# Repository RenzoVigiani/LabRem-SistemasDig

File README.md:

# Laboratorios de Sistemas digitales
En este readme se detallan las partes mas importantes del proyecto de remotización del laboratorio de **Sistemas digitales**, haciendo énfacis en el hardware.

## Protocolo para los laboratorios de "Sistemas Digitales"
Para poder establecer una comunicación entre al api web, generada por el equipo de software del proyecto, y los dispositivos en el laboratorio establecemos un protocolo en común. 

El procedimiento de comunicación es el siguiente.
Cada vez que se quiere modificar algun dato en el laboratorio. El Servidor debe enviar un...

```Ruby 
POST /HTTP/1.1 + <JSON a enviar>
```

##### Json a enviar (ejemplo)

```Ruby
{"Estado": [ 0, 1, 0],"velocidad": 9600, "Pulsadores": [0,1,1,0], "Serial": "Mensaje serial"}
```

Y para obtener avances de los datos o reporte de los datos debe enviar un:

```Ruby
GET /HTTP/1.1
```

De esta forma el Arduino responde ante una petición.

##### Json a recibir (ejemplo)

```Ruby
{"Estado": [ 0, true, false], "Velocidad":9600,"Indicadores": [false,false,false,false], "Serial": "Mensaje serial","Error":0}
```

## Sintaxis

**Estado**
Es un array conformado por 3 elementos en el siguiente orden: [Laboratorio, SubLab, Inicio del experimento]

|Laboratorio  | Sub Laboratorio  | Inicio del experimento | Laboratorio Seleccionado | Estado del experimento|
|-|-----|-----|------------------|--------|
|0|true |true |Comunicación UART |Inicia  |
|0|true |false|Comunicación UART |Finaliza|
|0|false|true |Comunicación I2C  |Inicia  |
|0|false|false|Comunicación I2C  |Finaliza|

>**Nota:** Los valores booleanos se los puede recibir en cualquier forma, es decir, <span style="color: green">_true=1=HIGH_ </span> y <span style="color: red">_false=0=LOW_</span>

**Velocidad**
Es un dato tipo entero que indica la velocidad de comunicación deseada.
*_ej: 9600, 115200, etc._

**Elementos por Laboratorio**
Laboratorio de UART

  - Utiliza **FPGA Cyclone II**    
    Nombre: Altera_FPGA_Board_EP2C8Q208C8 Cyclone II
    
  - Pulsadores: [Pulsador1, Pulsador2, Pulsador3, Pulsador4]
  - Indicadores: [indicador1, indicador2, indicador3, indicador4]

Laboratorio de I2C

  - Utiliza **FPGA Cyclone IV**
    Nombre: Altera_FPGA_Board_EP4CE6E22C8 Cyclone IV

  - Pulsadores: [Pulsador1, Pulsador2,Pulsador3,Pulsador4 ]
  - Indicadores:  [indicador1, indicador2, indicador3, indicador4]

>Los mismos son utilizados para representar en la API lo que se ve por la WebCam.

**Serial:** Es un dato del tipo "string" con un tamaño maximo de 100 caracteres.

**Error:** Es una variable numerica que representa un mensaje de error.

| Tipo de error                         |  Valor  |
| ----------------------------------    |---------|
| Sin errores                           |    0    |
| Error limites de angulo de azimut.    |    1    |
| Error limites de angulo de elevación  |    2    |
| Error de laboratorio incorrecto       |    3    |

## Diagramas

**Esquematico general**

**Esquematico**

**Arduino Mega 2560: Pin Out**

 **Adaptadores de nivel**

## *Diseños 3D*
Para cada una de las placas se realizaron bases y soportes para las placas para poder identificar a cada una y que se pueda diferencias con facilidad desde el usuario.

||||
|-|-|-|
||||
||||
||||
||||

**Datasheets**
- [Recopilación de Datasheets](https://renzovigiani.notion.site/adea4f735c994faaa2f919a7e5105e9d?v=83070c8c05d34c02905fc370e37b802a)
- [Altera Cyclone II](https://pdf.utmel.com/r/datasheets/altera-ep2c8q208c8n-datasheets-8218.pdf)
- [Altera Cyclone IV](https://docs.rs-online.com/6ee7/0900766b80f69ead.pdf)
- [Adaptadores de Nivel 1](https://www.ti.com/lit/ds/symlink/txs0108e.pdf?ts=1659067269078&ref_url=https%253A%252F%252Fwww.ti.com%252Fproduct%252FTXS0108E)
- [Adaptadores de Nivel 2](https://components101.com/modules/txs0108e-bi-directional-logic-level-converter-module)

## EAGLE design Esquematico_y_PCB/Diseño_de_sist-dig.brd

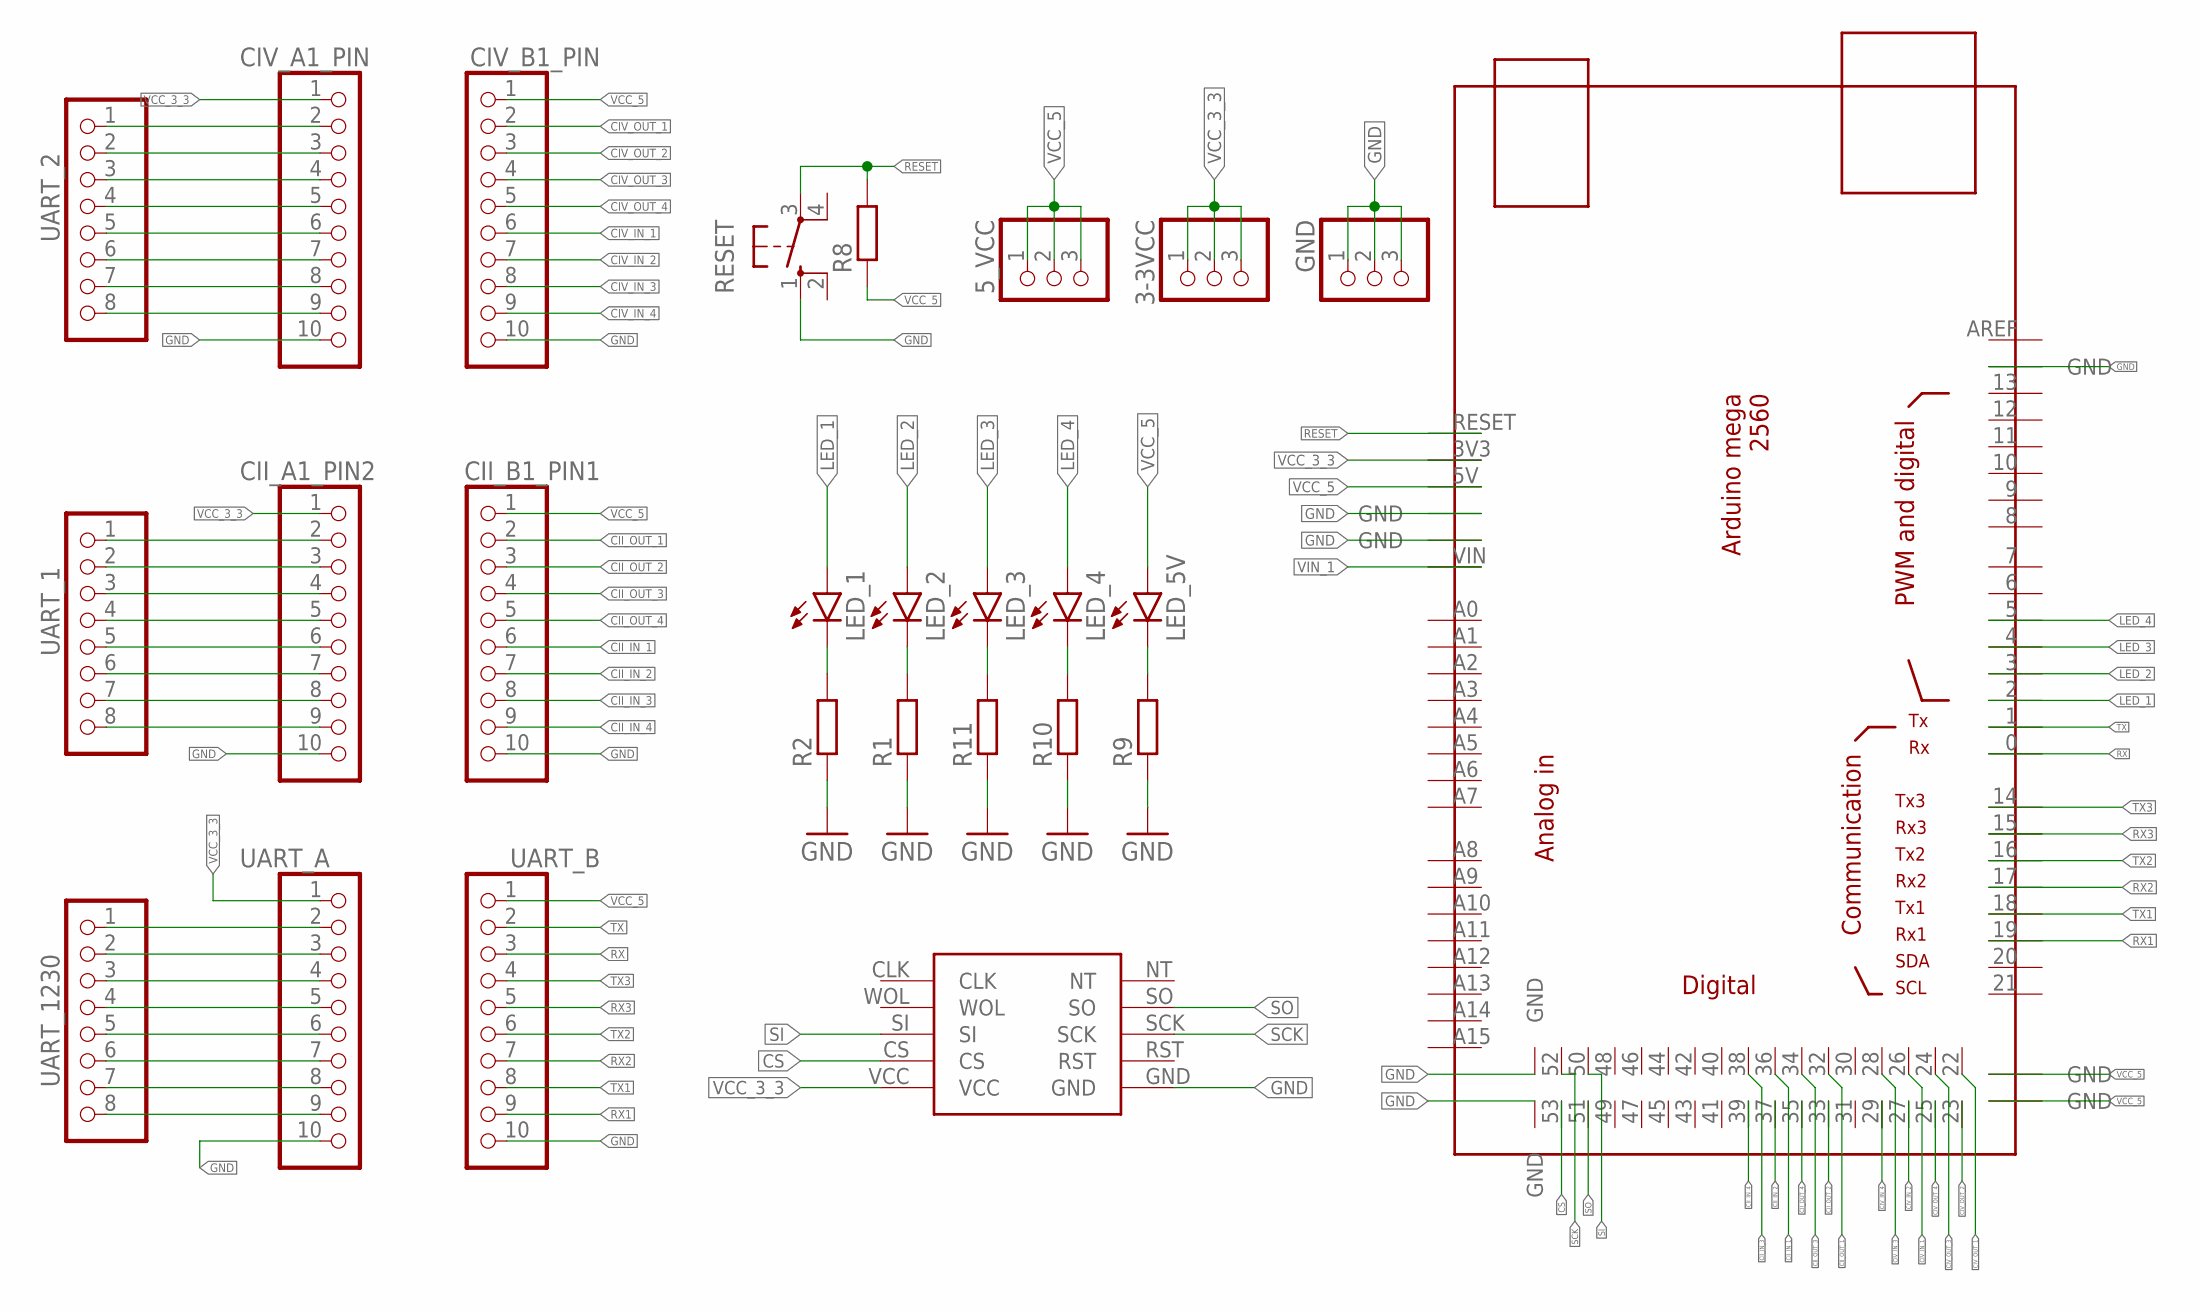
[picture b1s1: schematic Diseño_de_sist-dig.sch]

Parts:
3-3VCC, 5_VCC: PINHD-1X3; 1X03
ARDUINOMEGA2560: MEGA_DEVICE; MEGAOUTLINE
CII_A1_PIN2: PINHD-1X10; 1X10-BIG
CII_B1_PIN1: PINHD-1X10; 1X10-BIG
CIV_A1_PIN: PINHD-1X10; 1X10-BIG
CIV_B1_PIN: PINHD-1X10; 1X10-BIG
GND: PINHD-1X3; 1X03
LED_1, LED_2, LED_3, LED_4, LED_5V: LED3MM
MODULO_ETHERNET: ENC28J60
R1, R2, R8, R9, R10, R11: R_CHIP-0805(2012-METRIC); RESC2012X65
RESET: 10-XX; B3F-10XX
UART_1, UART_2, UART_1230: PINHD-1X8CLEANBIG; 1X08-CLEANBIG
UART_A: PINHD-1X10; 1X10-BIG
UART_B: PINHD-1X10; 1X10-BIG

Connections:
CII_IN_1: ARDUINOMEGA2560.36, CII_B1_PIN1.6
CII_IN_2: ARDUINOMEGA2560.37, CII_B1_PIN1.7
CII_IN_3: ARDUINOMEGA2560.38, CII_B1_PIN1.8
CII_IN_4: ARDUINOMEGA2560.39, CII_B1_PIN1.9
CII_OUT_1: ARDUINOMEGA2560.32, CII_B1_PIN1.2
CII_OUT_2: ARDUINOMEGA2560.33, CII_B1_PIN1.3
CII_OUT_3: ARDUINOMEGA2560.34, CII_B1_PIN1.4
CII_OUT_4: ARDUINOMEGA2560.35, CII_B1_PIN1.5
CIV_IN_1: ARDUINOMEGA2560.26, CIV_B1_PIN.6
CIV_IN_2: ARDUINOMEGA2560.27, CIV_B1_PIN.7
CIV_IN_3: ARDUINOMEGA2560.28, CIV_B1_PIN.8
CIV_IN_4: ARDUINOMEGA2560.29, CIV_B1_PIN.9
CIV_OUT_1: ARDUINOMEGA2560.22, CIV_B1_PIN.2
CIV_OUT_2: ARDUINOMEGA2560.23, CIV_B1_PIN.3
CIV_OUT_3: ARDUINOMEGA2560.24, CIV_B1_PIN.4
CIV_OUT_4: ARDUINOMEGA2560.25, CIV_B1_PIN.5
CS: ARDUINOMEGA2560.53, MODULO_ETHERNET.CS
GND: ARDUINOMEGA2560.GND@1 (GND), ARDUINOMEGA2560.GND@2 (GND), ARDUINOMEGA2560.GND@3 (GND), ARDUINOMEGA2560.GND@6 (GND), ARDUINOMEGA2560.GND@7 (GND), CII_A1_PIN2.10, CII_B1_PIN1.10, CIV_A1_PIN.10, CIV_B1_PIN.10, GND.1, GND.2, GND.3, MODULO_ETHERNET.GND, R1.1, R2.1, R9.1, R10.1, R11.1, RESET.1 (S), UART_A.10, UART_B.10
LED_1: ARDUINOMEGA2560.2, LED_1.A
LED_2: ARDUINOMEGA2560.3, LED_2.A
LED_3: ARDUINOMEGA2560.4, LED_3.A
LED_4: ARDUINOMEGA2560.5, LED_4.A
unnamed: LED_2.K (C), R1.2
unnamed: LED_1.K (C), R2.2
unnamed: UART_1230.1, UART_A.2
unnamed: LED_5V.K (C), R9.2
unnamed: LED_4.K (C), R10.2
unnamed: LED_3.K (C), R11.2
unnamed: UART_1230.2, UART_A.3
unnamed: UART_1230.3, UART_A.4
unnamed: UART_1230.4, UART_A.5
unnamed: UART_1230.5, UART_A.6
unnamed: UART_1230.6, UART_A.7
unnamed: UART_1230.7, UART_A.8
unnamed: UART_1230.8, UART_A.9
unnamed: CII_A1_PIN2.2, UART_1.1
unnamed: CIV_A1_PIN.2, UART_2.1
unnamed: CIV_A1_PIN.3, UART_2.2
unnamed: CIV_A1_PIN.4, UART_2.3
unnamed: CIV_A1_PIN.5, UART_2.4
unnamed: CIV_A1_PIN.6, UART_2.5
unnamed: CIV_A1_PIN.7, UART_2.6
unnamed: CIV_A1_PIN.8, UART_2.7
unnamed: CIV_A1_PIN.9, UART_2.8
unnamed: CII_A1_PIN2.3, UART_1.2
unnamed: CII_A1_PIN2.4, UART_1.3
unnamed: CII_A1_PIN2.5, UART_1.4
unnamed: CII_A1_PIN2.6, UART_1.5
unnamed: CII_A1_PIN2.7, UART_1.6
unnamed: CII_A1_PIN2.8, UART_1.7
unnamed: CII_A1_PIN2.9, UART_1.8
RESET: ARDUINOMEGA2560.RESET, R8.2, RESET.3
RX: ARDUINOMEGA2560.0, UART_B.3
RX1: ARDUINOMEGA2560.19, UART_B.9
RX2: ARDUINOMEGA2560.17, UART_B.7
RX3: ARDUINOMEGA2560.15, UART_B.5
SCK: ARDUINOMEGA2560.52, MODULO_ETHERNET.SCK
SI: ARDUINOMEGA2560.50, MODULO_ETHERNET.SI
SO: ARDUINOMEGA2560.51, MODULO_ETHERNET.SO
TX: ARDUINOMEGA2560.1, UART_B.2
TX1: ARDUINOMEGA2560.18, UART_B.8
TX2: ARDUINOMEGA2560.16, UART_B.6
TX3: ARDUINOMEGA2560.14, UART_B.4
VCC_3_3: 3-3VCC.1, 3-3VCC.2, 3-3VCC.3, ARDUINOMEGA2560.3V3, CII_A1_PIN2.1, CIV_A1_PIN.1, MODULO_ETHERNET.VCC, UART_A.1
VCC_5: 5_VCC.1, 5_VCC.2, 5_VCC.3, ARDUINOMEGA2560.5V, ARDUINOMEGA2560.GND@4 (GND), ARDUINOMEGA2560.GND@5 (GND), CII_B1_PIN1.1, CIV_B1_PIN.1, LED_5V.A, R8.1, UART_B.1
VIN_1: ARDUINOMEGA2560.VIN

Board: 2 copper layers, 26 parts (0 on the bottom side), 65 nets, no tracks yet.

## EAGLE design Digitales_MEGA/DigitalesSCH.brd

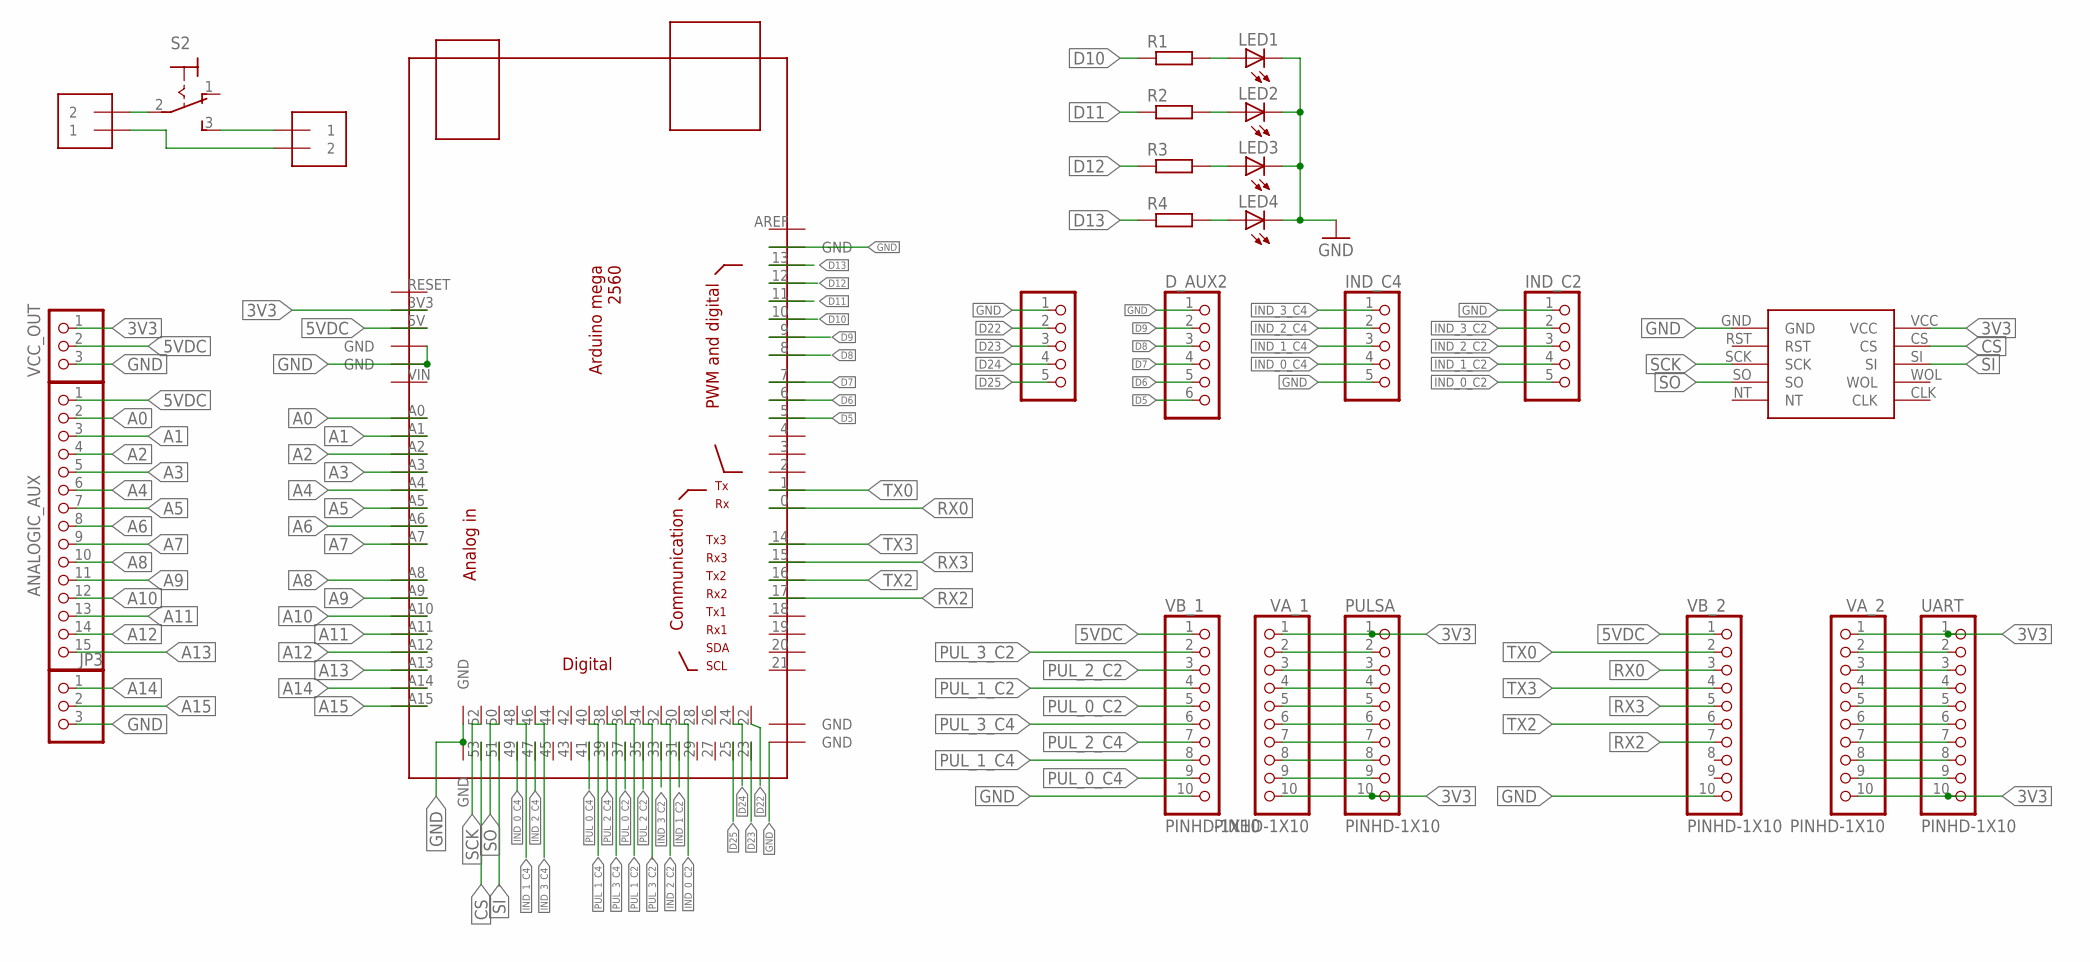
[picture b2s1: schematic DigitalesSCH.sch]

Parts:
ANALOGIC_AUX: PINHD-1X15; 1X15
D_AUX1: PINHD-1X5; 1X05
D_AUX2: PINHD-1X6; 1X06
IND_C2, IND_C4: PINHD-1X5; 1X05
JP3: PINHD-1X3; 1X03
LED1, LED2, LED3, LED4: LED3MM
PULSA: PINHD-1X10; 1X10-BIG
R1, R2, R3, R4: R-EU_M1206; M1206
S2: M9040P
U$1: MEGA_DEVICE; MEGAOUTLINE
U$2: ENC28J60
UART: PINHD-1X10; 1X10-BIG
VA_1, VA_2: PINHD-1X10; 1X10-BIG
VB_1, VB_2: PINHD-1X10; 1X10-BIG
VCC_OUT: PINHD-1X3; 1X03
VIN: 1X2-3.5MM
VOUT: 1X2-3.5MM

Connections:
3V3: PULSA.1, PULSA.10, U$1.3V3, U$2.VCC, UART.1, UART.10, VA_1.1, VA_1.10, VA_2.1, VA_2.10, VCC_OUT.1
5VDC: ANALOGIC_AUX.1, U$1.5V, VB_1.1, VB_2.1, VCC_OUT.2
A0: ANALOGIC_AUX.2, U$1.A0
A1: ANALOGIC_AUX.3, U$1.A1
A2: ANALOGIC_AUX.4, U$1.A2
A3: ANALOGIC_AUX.5, U$1.A3
A4: ANALOGIC_AUX.6, U$1.A4
A5: ANALOGIC_AUX.7, U$1.A5
A6: ANALOGIC_AUX.8, U$1.A6
A7: ANALOGIC_AUX.9, U$1.A7
A8: ANALOGIC_AUX.10, U$1.A8
A9: ANALOGIC_AUX.11, U$1.A9
A10: ANALOGIC_AUX.12, U$1.A10
A11: ANALOGIC_AUX.13, U$1.A11
A12: ANALOGIC_AUX.14, U$1.A12
A13: ANALOGIC_AUX.15, U$1.A13
A14: JP3.1, U$1.A14
A15: JP3.2, U$1.A15
CS: U$1.53, U$2.CS
D5: D_AUX2.6, U$1.5
D6: D_AUX2.5, U$1.6
D7: D_AUX2.4, U$1.7
D8: D_AUX2.3, U$1.8
D9: D_AUX2.2, U$1.9
D10: R1.1, U$1.10
D11: R2.1, U$1.11
D12: R3.1, U$1.12
D13: R4.1, U$1.13
D22: D_AUX1.2, U$1.22
D23: D_AUX1.3, U$1.23
D24: D_AUX1.4, U$1.24
D25: D_AUX1.5, U$1.25
GND: D_AUX1.1, D_AUX2.1, IND_C2.1, IND_C4.5, JP3.3, LED1.K (C), LED2.K (C), LED3.K (C), LED4.K (C), U$1.GND@1 (GND), U$1.GND@2 (GND), U$1.GND@3 (GND), U$1.GND@5 (GND), U$1.GND@6 (GND), U$1.GND@7 (GND), U$2.GND, VB_1.10, VB_2.10, VCC_OUT.3
IND_0_C2: IND_C2.5, U$1.30
IND_0_C4: IND_C4.4, U$1.49
IND_1_C2: IND_C2.4, U$1.31
IND_1_C4: IND_C4.3, U$1.48
IND_2_C2: IND_C2.3, U$1.32
IND_2_C4: IND_C4.2, U$1.47
IND_3_C2: IND_C2.2, U$1.33
IND_3_C4: IND_C4.1, U$1.46
unnamed: LED1.A, R1.2
unnamed: LED2.A, R2.2
unnamed: LED3.A, R3.2
unnamed: LED4.A, R4.2
unnamed: S2.2, VIN.2
unnamed: PULSA.2, VA_1.2
unnamed: PULSA.3, VA_1.3
unnamed: PULSA.4, VA_1.4
unnamed: PULSA.5, VA_1.5
unnamed: PULSA.6, VA_1.6
unnamed: PULSA.7, VA_1.7
unnamed: PULSA.8, VA_1.8
unnamed: PULSA.9, VA_1.9
unnamed: S2.3 (S), VOUT.1
unnamed: VIN.1, VOUT.2
unnamed: UART.2, VA_2.2
unnamed: UART.3, VA_2.3
unnamed: UART.4, VA_2.4
unnamed: UART.5, VA_2.5
unnamed: UART.6, VA_2.6
unnamed: UART.7, VA_2.7
unnamed: UART.8, VA_2.8
unnamed: UART.9, VA_2.9
PUL_0_C2: U$1.37, VB_1.5
PUL_0_C4: U$1.41, VB_1.9
PUL_1_C2: U$1.36, VB_1.4
PUL_1_C4: U$1.40, VB_1.8
PUL_2_C2: U$1.35, VB_1.3
PUL_2_C4: U$1.39, VB_1.7
PUL_3_C2: U$1.34, VB_1.2
PUL_3_C4: U$1.38, VB_1.6
RX0: U$1.0, VB_2.3
RX2: U$1.17, VB_2.7
RX3: U$1.15, VB_2.5
SCK: U$1.52, U$2.SCK
SI: U$1.51, U$2.SI
SO: U$1.50, U$2.SO
TX0: U$1.1, VB_2.2
TX2: U$1.16, VB_2.6
TX3: U$1.14, VB_2.4

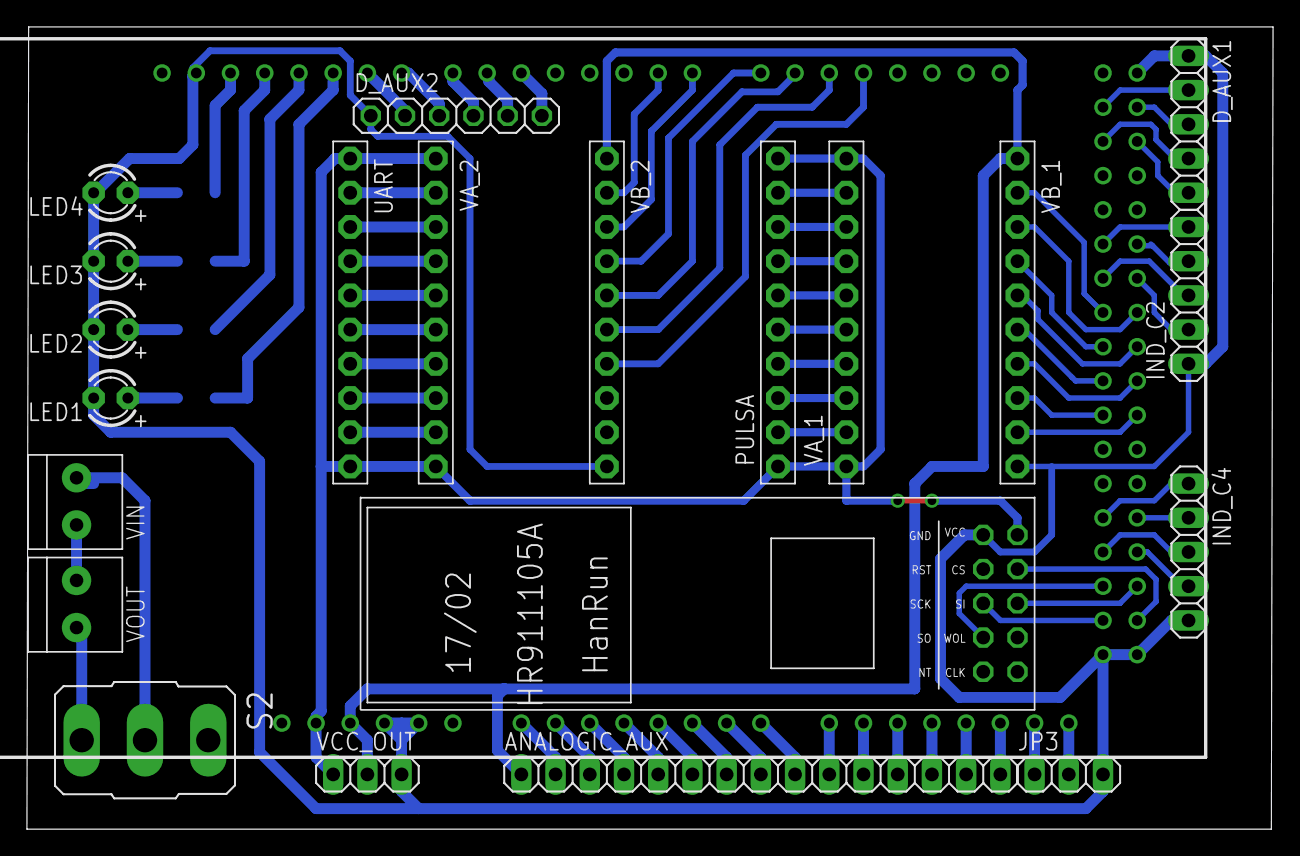
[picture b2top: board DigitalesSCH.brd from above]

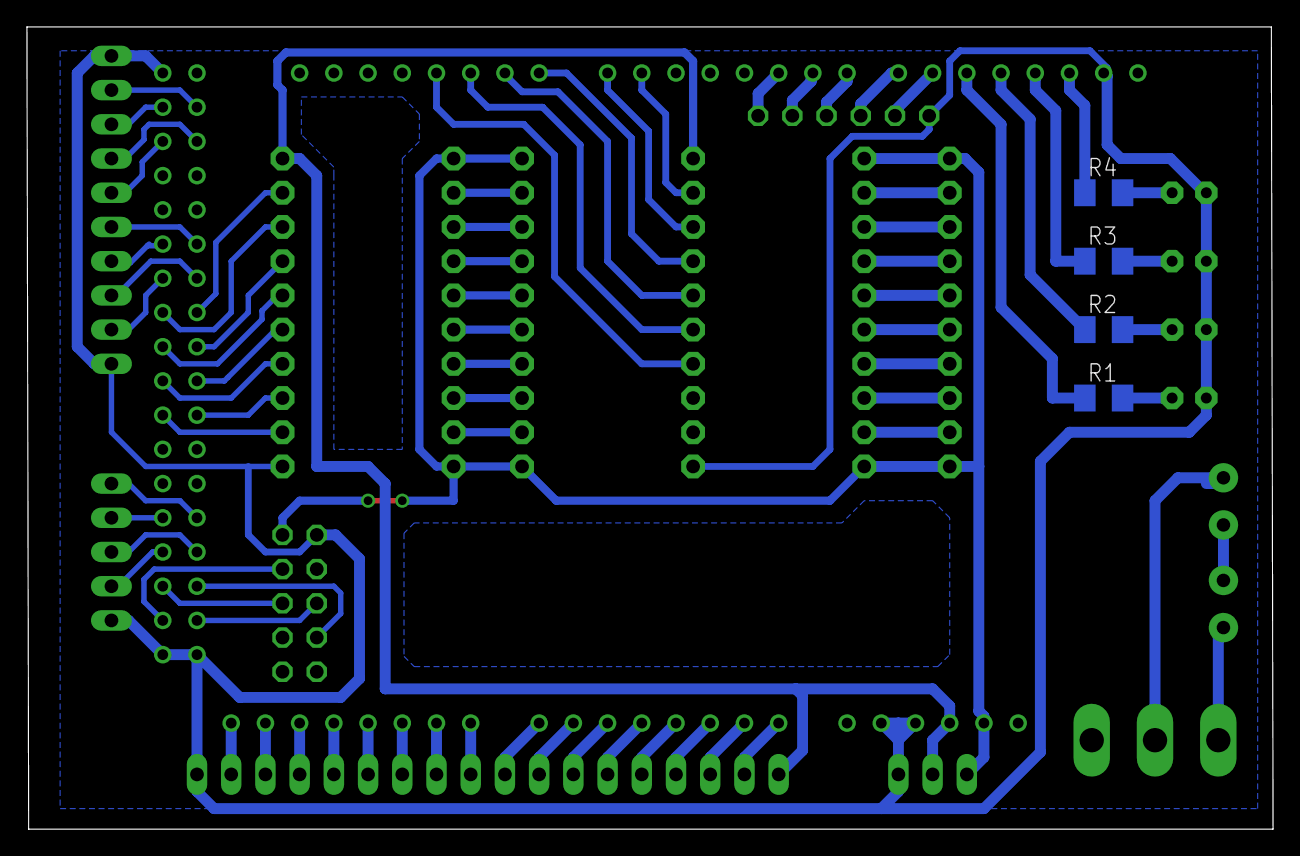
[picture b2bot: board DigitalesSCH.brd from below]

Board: 2 copper layers, 92.5 x 59.6 mm, 26 parts (4 on the bottom side), 81 nets.

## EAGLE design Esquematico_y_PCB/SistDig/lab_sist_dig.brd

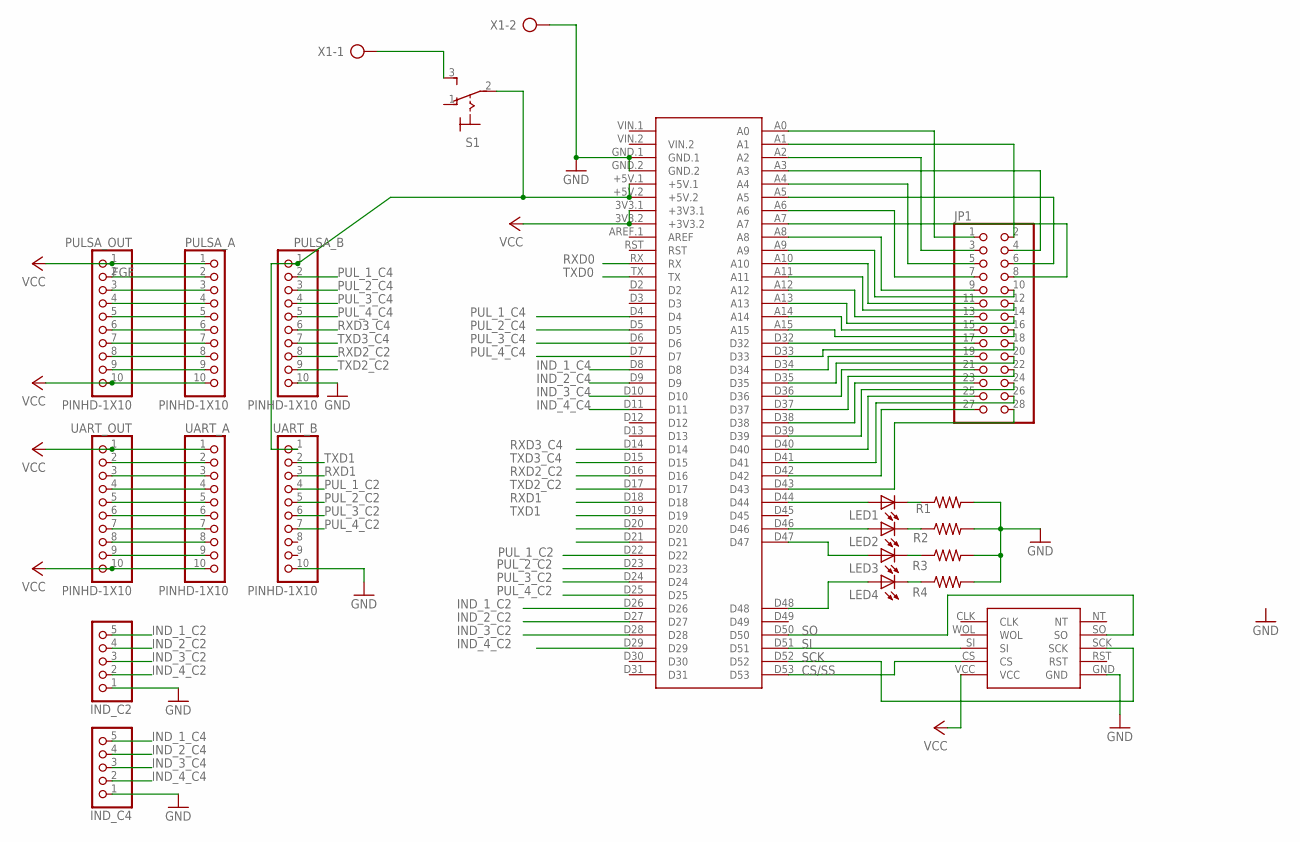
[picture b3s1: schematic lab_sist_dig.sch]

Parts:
IND_C2, IND_C4: PINHD-1X5; 1X05
JP1: PINHD-2X14; 2X14
LED1, LED2, LED3, LED4: LED3MM
PULSA_A: PINHD-1X10; 1X10-BIG
PULSA_B: PINHD-1X10; 1X10-BIG
PULSA_OUT: PINHD-1X10; 1X10-BIG
R1, R2, R3, R4: FLIPFLOP-RES; 0805-THM
S1: 320-916
U$1: MEGA2560_MIKRO
U$2: ENC28J60
UART_A: PINHD-1X10; 1X10-BIG
UART_B: PINHD-1X10; 1X10-BIG
UART_OUT: PINHD-1X10; 1X10-BIG
X1: AK300/2

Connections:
CS/SS: U$1.D53, U$2.CS
FGF: PULSA_A.2, PULSA_OUT.2
GND: IND_C2.1, IND_C4.1, PULSA_B.10, R1.2, R2.2, R3.2, R4.2, U$1.GND.1, U$1.GND.2, U$2.GND, UART_B.10, X1.2
IND_1_C2: IND_C2.5, U$1.D26
IND_1_C4: IND_C4.5, U$1.D8
IND_2_C2: IND_C2.4, U$1.D27
IND_2_C4: IND_C4.4, U$1.D9
IND_3_C2: IND_C2.3, U$1.D28
IND_3_C4: IND_C4.3, U$1.D10
IND_4_C2: IND_C2.2, U$1.D29
IND_4_C4: IND_C4.2, U$1.D11
unnamed: LED1.A, U$1.D44
unnamed: LED2.A, U$1.D46
unnamed: PULSA_A.3, PULSA_OUT.3
unnamed: PULSA_A.4, PULSA_OUT.4
unnamed: PULSA_A.5, PULSA_OUT.5
unnamed: PULSA_A.6, PULSA_OUT.6
unnamed: PULSA_A.7, PULSA_OUT.7
unnamed: PULSA_A.8, PULSA_OUT.8
unnamed: PULSA_A.9, PULSA_OUT.9
unnamed: UART_A.2, UART_OUT.2
unnamed: PULSA_B.1, S1.2, U$1.+5V.1, U$1.+5V.2, UART_B.1
unnamed: UART_A.3, UART_OUT.3
unnamed: UART_A.5, UART_OUT.5
unnamed: UART_A.4, UART_OUT.4
unnamed: UART_A.6, UART_OUT.6
unnamed: UART_A.7, UART_OUT.7
unnamed: UART_A.8, UART_OUT.8
unnamed: UART_A.9, UART_OUT.9
unnamed: S1.3 (S), X1.1
unnamed: JP1.1, U$1.A0
unnamed: JP1.2, U$1.A1
unnamed: JP1.3, U$1.A2
unnamed: JP1.7, U$1.A6
unnamed: JP1.5, U$1.A4
unnamed: JP1.6, U$1.A5
unnamed: LED3.A, U$1.D47
unnamed: LED4.A, U$1.D48
unnamed: LED1.K (C), R1.1
unnamed: LED2.K (C), R2.1
unnamed: JP1.4, U$1.A3
unnamed: LED3.K (C), R3.1
unnamed: LED4.K (C), R4.1
unnamed: JP1.8, U$1.A7
unnamed: JP1.9, U$1.A8
unnamed: JP1.11, U$1.A10
unnamed: JP1.13, U$1.A12
unnamed: JP1.15, U$1.A14
unnamed: JP1.17, U$1.D32
unnamed: JP1.19, U$1.D34
unnamed: JP1.21, U$1.D36
unnamed: JP1.23, U$1.D38
unnamed: JP1.25, U$1.D40
unnamed: JP1.16, U$1.A15
unnamed: JP1.10, U$1.A9
unnamed: JP1.20, U$1.D35
unnamed: JP1.12, U$1.A11
unnamed: JP1.14, U$1.A13
unnamed: JP1.18, U$1.D33
unnamed: JP1.22, U$1.D37
unnamed: JP1.24, U$1.D39
unnamed: JP1.26, U$1.D41
unnamed: JP1.27, U$1.D42
unnamed: JP1.28, U$1.D43
PUL_1_C2: U$1.D22, UART_B.4
PUL_1_C4: PULSA_B.2, U$1.D4
PUL_2_C2: U$1.D23, UART_B.5
PUL_2_C4: PULSA_B.3, U$1.D5
PUL_3_C2: U$1.D24, UART_B.6
PUL_3_C4: PULSA_B.4, U$1.D6
PUL_4_C2: U$1.D25, UART_B.7
PUL_4_C4: PULSA_B.5, U$1.D7
RXD0: U$1.RX
RXD1: U$1.D18, UART_B.3
RXD2_C2: PULSA_B.8, U$1.D16
RXD3_C4: PULSA_B.6, U$1.D14
SCK: U$1.D52, U$2.SCK
SI: U$1.D51, U$2.SI
SO: U$1.D50, U$2.SO
TXD0: U$1.TX
TXD1: U$1.D19, UART_B.2
TXD2_C2: PULSA_B.9, U$1.D17
TXD3_C4: PULSA_B.7, U$1.D15
VCC: PULSA_A.1, PULSA_A.10, PULSA_OUT.1, PULSA_OUT.10, U$1.3V3.1 (+3V3.1), U$1.3V3.2 (+3V3.2), U$2.VCC, UART_A.1, UART_A.10, UART_OUT.1, UART_OUT.10

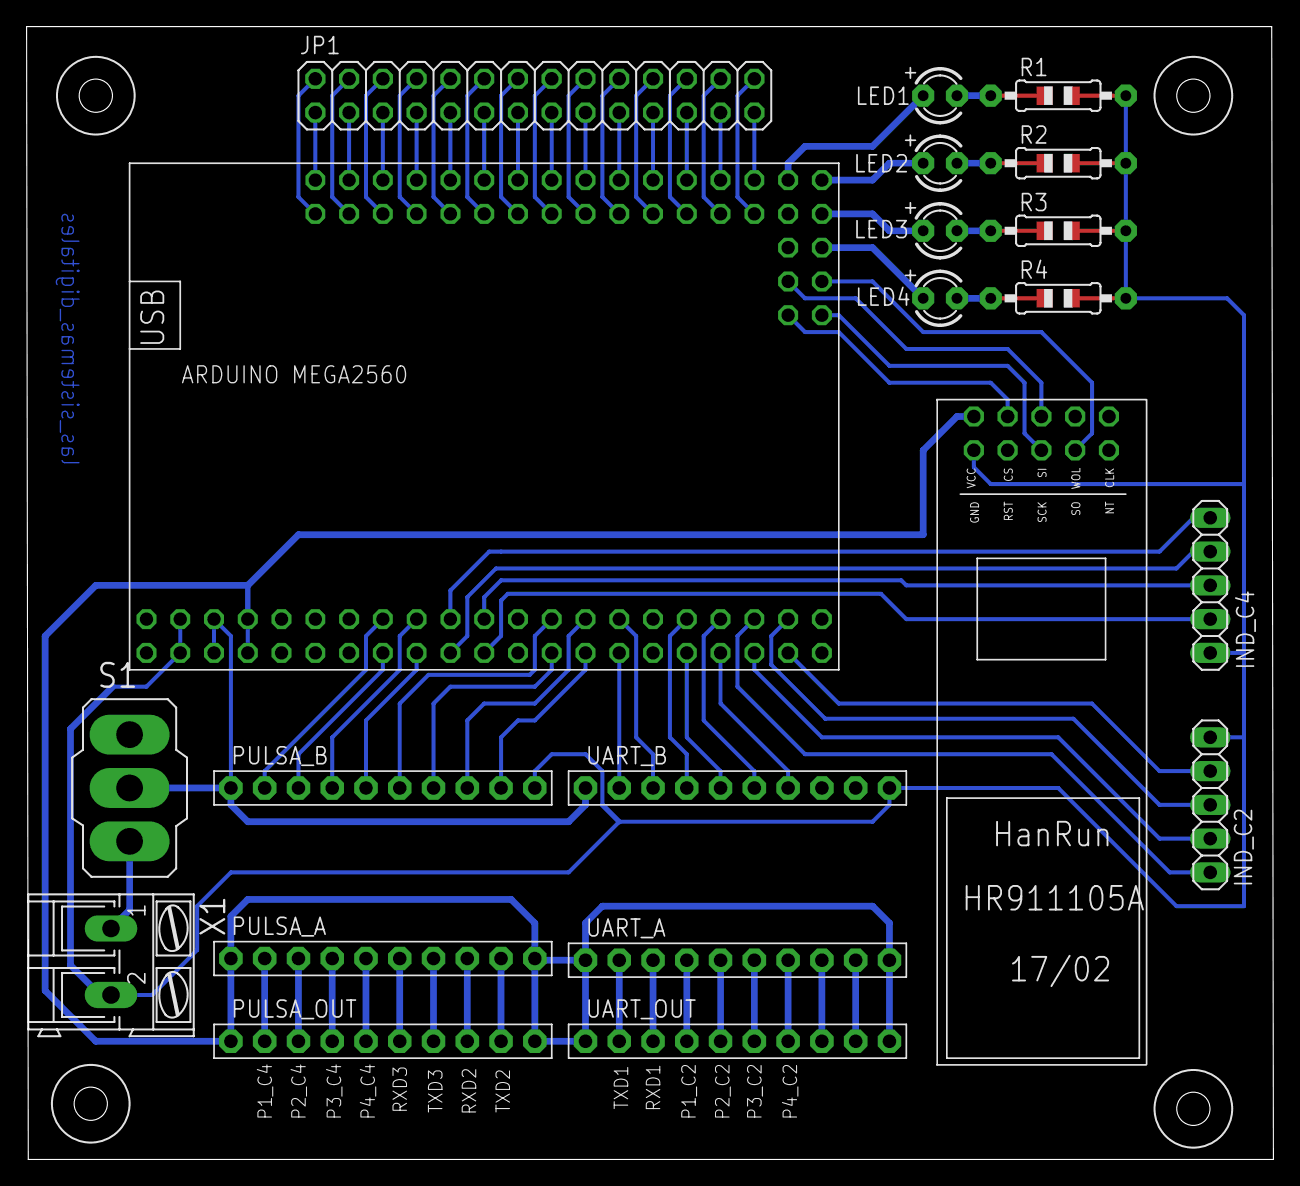
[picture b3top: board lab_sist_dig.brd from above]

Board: 2 copper layers, 93.8 x 85.2 mm, 25 parts (0 on the bottom side), 82 nets.

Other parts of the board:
U$3, U$4, U$5, U$6: DRIL-2,5

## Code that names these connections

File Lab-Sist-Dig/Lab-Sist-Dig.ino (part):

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  int repeticiones=0; // contador para repeticiones.

//--- FUNCIONES --- //
  void asignarPines(int pul_0,int pul_1,int pul_2,int pul_3,int led_0,int led_1,int led_2,int led_3);
  void Comunicacion(bool Serial_out);
  void Control();
  
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 * @param led_2 - Indicador 2
 * @param led_3 - Indicador 3
 */
void asignarPines(int pul_0,int pul_1,int pul_2,int pul_3,int led_0,int led_1,int led_2,int led_3){
//    Serial.println("Escribo pulsadores");
    digitalWrite(pul_0,pulsador_0);
    digitalWrite(pul_1,pulsador_1);
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
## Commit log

2022-05-04 Init Commit - se realizaron pruebas en la comunicación JSON
2022-05-04 Cambio de nombre al archivo principal
2022-05-04 Se agregan las salidas ( Motores y actuadores). Se prueba con comunicación JSON. Se prueba el correcto funcionamiento del motor paso a paso como prueba general.
2022-05-04 Se realiza las pruebas de comunicación por UART. utilizando software seria y un arduino que simula FPGA Se optimiza el codigo y la memoria ram estableciendo variables locales. Se crean funciones para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
2022-05-04 Actualización del protocolo.
2022-05-08 Ajustes en readme
2022-05-09 Cambioes en readme.md Se utiliza un Json distinto para enviar y recibir.
2022-05-10 Corrección del Lab segun protocolo.
2022-05-16 ajustes uart
2022-05-16 se agragan archivos para programamar FPGA
2022-05-17 fpga_uart
2022-05-17 Modificaciones en vhdl para manejar fpga - prueba.
2022-05-23 Cambios en protocolo de envío
2022-05-24 Actualización de PinOut
2022-05-24 Actualización de Readme
2022-05-27 Incorporación Archivos esquematicos
2022-06-01 Esquematico y PCB completos
2022-06-01 PCB y Esquematico
2022-07-03 Protocolo de comunicación Se realizó la actualización del protocolo de comunicación
2022-07-13 Esquematico para arduino mega
2022-07-13 prueba
2022-07-14 Actualizo Readme
2022-07-14 Actualización de comunicación
2022-07-14 nueva confirmación
2022-07-15 Programa p/el arduino mega. Modif nombres pinout
2022-07-20 Llave de encendico al esquematico y pcb
2022-07-21 Actaulización PCB y SCH
2022-07-21 Asisgnación de pines para las pruebas
2022-07-29 cambios en Readme Pruebas en UART con fpga
2022-08-02 Actualización comunicación UART entre arduinos Con protocolo.
2022-08-03 Solucionado comunicación UART Entre arduinos con protocolo.
2022-08-03 Actualización de readme.md y ordenado de codigo
2022-09-22 diseño pcb - ver comunicacion uart y terminar pcb
2022-11-24 omagenes agregadas
2022-11-25 Actualización Readme
2023-05-25 Diseño node red
